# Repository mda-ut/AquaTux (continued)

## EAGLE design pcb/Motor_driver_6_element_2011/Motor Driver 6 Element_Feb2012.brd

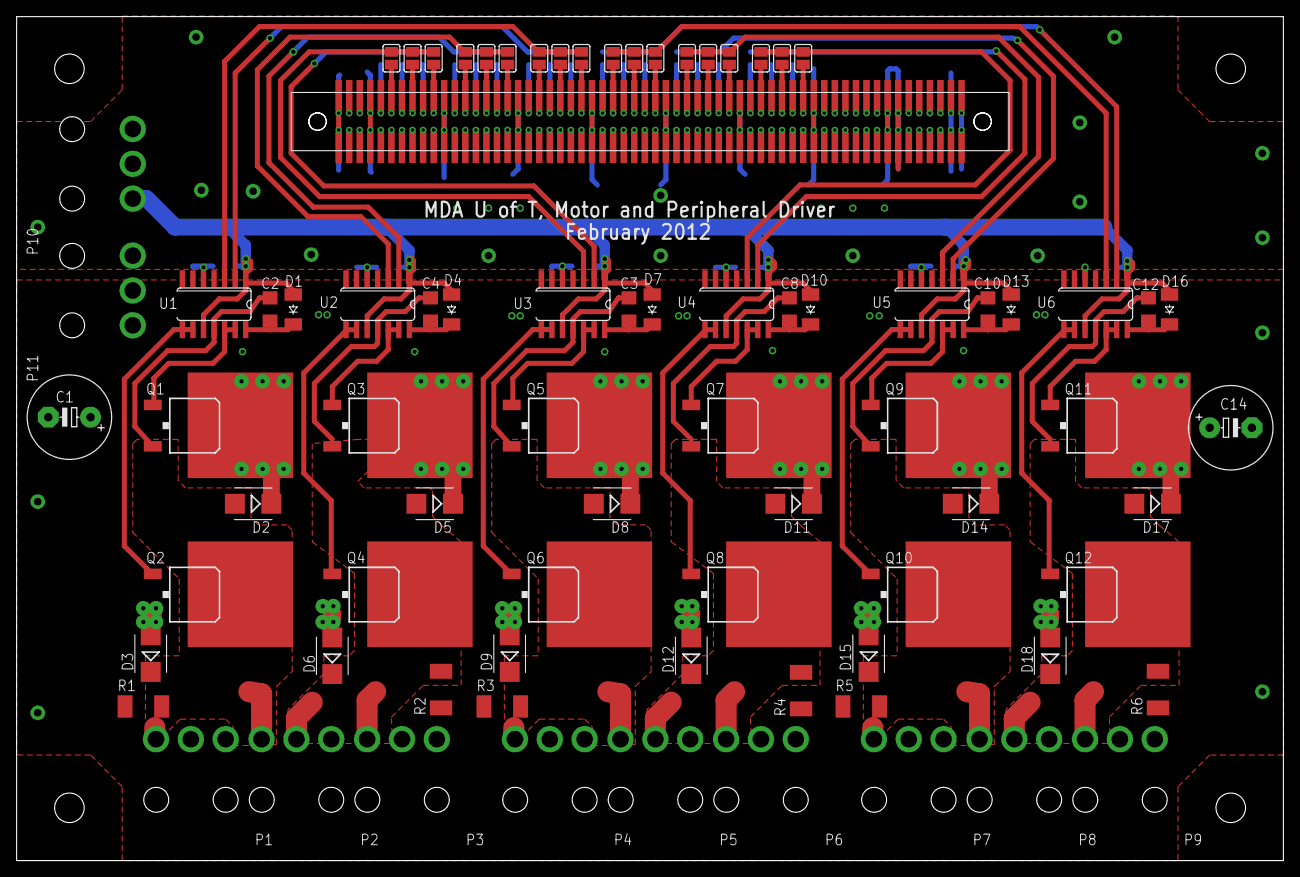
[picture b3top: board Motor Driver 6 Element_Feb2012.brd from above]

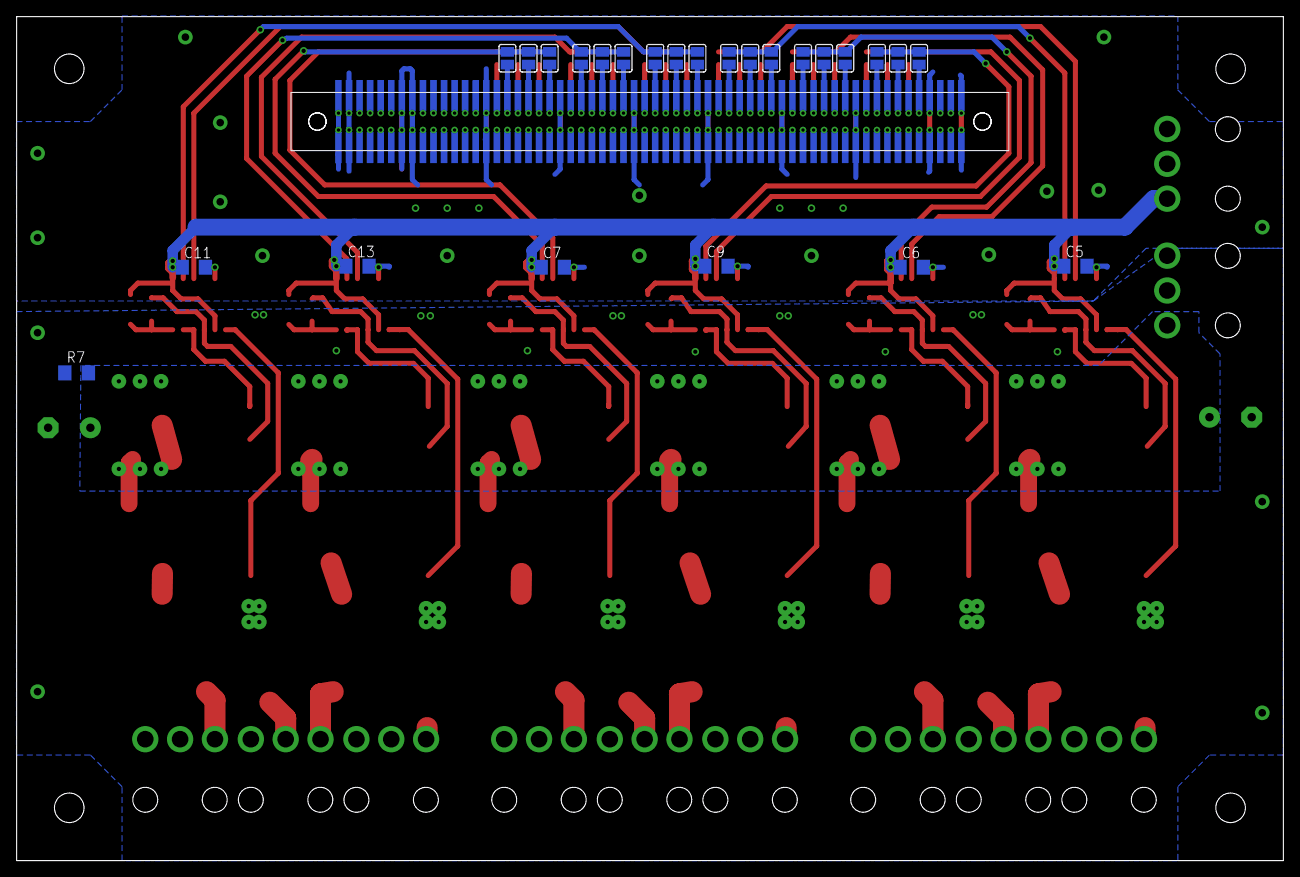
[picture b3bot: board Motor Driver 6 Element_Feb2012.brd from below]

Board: 2 copper layers, 152.4 x 101.5 mm, 106 parts (26 on the bottom side), 136 nets.

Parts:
C1, C14: >100uF; E5-10,5
C2, C3, C4, C8, C10, C12: 1uF; C1206
C5, C6, C7, C9, C11, C13: 10uF; C1206@1
D1, D4, D7, D10, D13, D16: CGRM4001-G; SOD-123_MINI-SMA
D2, D3, D5, D6, D8, D9, D11, D12, D14, D15, D17, D18: SMB
E$1, E$2: STACK-CONN-WIDEPITCH
P1, P2, P3, P4, P5, P6, P7, P8, P9, P10, P11: MOLEX_MINIFIT_JR_3CKT; 3CKT_MINIFIT_JR
Q1, Q2, Q3, Q4, Q5, Q6, Q7, Q8, Q9, Q10, Q11, Q12: IPB70N04S3; D-PAK_TO252AA
R1, R2, R3, R4, R5, R6: 1.5k; R2010
R7: R1206
SJ1, SJ2, SJ3, SJ4, SJ5, SJ6, SJ7, SJ8, SJ9, SJ10, SJ11, SJ12, SJ13, SJ14, SJ15, SJ16, SJ17, SJ18, SJ19, SJ21, SJ22, SJ23, SJ24, SJ25, SJ26, SJ27, SJ28, SJ29, SJ30, SJ31, SJ32, SJ33, SJ34, SJ35, SJ36, SJ37: SJ
U1, U2, U3, U4, U5, U6: LT1160CS; SOIC14

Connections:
+12V: C5.1, C6.1, C7.1, C9.1, C11.1, C13.1, D1.A, D4.A, D7.A, D10.A, D13.A, D16.A, P10.3, U1.1, U1.10, U2.1, U2.10, U3.1, U3.10, U4.1, U4.10, U5.1, U5.10, U6.1, U6.10
+24V: C1.+, C14.+, P11.3, R7.2
AGND: C1.-, C14.-, D3.A, D6.A, D9.A, D12.A, D15.A, D18.A, P1.3, P3.3, P4.3, P6.3, P7.3, P9.3, P11.2, Q2.3, Q4.3, Q6.3, Q8.3, Q10.3, Q12.3, R1.1, R2.1, R3.1, R4.1, R5.1, R6.1, R7.1, U1.6, U2.6, U3.6, U4.6, U5.6, U6.6
GND: C5.2, C6.2, C7.2, C9.2, C11.2, C13.2, E$1.A1, E$1.A2, E$1.A7, E$1.A8, E$1.A15, E$1.A22, E$1.A29, E$1.A36, E$1.A43, E$1.A50, E$1.A57, E$1.A60, E$1.B1, E$1.B2, E$1.B7, E$1.B8, E$1.B15, E$1.B22, E$1.B29, E$1.B36, E$1.B43, E$1.B50, E$1.B57, E$1.B60, E$2.A1, E$2.A4, E$2.A11, E$2.A18, E$2.A25, E$2.A32, E$2.A39, E$2.A46, E$2.A53, E$2.A54, E$2.A60, E$2.B1, E$2.B4, E$2.B11, E$2.B18, E$2.B25, E$2.B32, E$2.B39, E$2.B46, E$2.B53, E$2.B54, E$2.B59, E$2.B60, U1.5, U2.5, U3.5, U4.5, U5.5, U6.5
unnamed: C2.1, D1.C, U1.14
unnamed: SJ5.2, SJ6.2, SJ7.2, U3.3
unnamed: C3.1, D7.C, U3.14
unnamed: SJ2.2, SJ3.2, SJ4.2, U3.2
unnamed: SJ17.2, SJ18.2, U1.3
unnamed: Q1.1, U1.12, U1.13
unnamed: Q5.1, U3.12, U3.13
unnamed: C8.1, D10.C, U4.14
unnamed: Q8.1, U4.8, U4.9
unnamed: SJ21.2, U4.2
unnamed: SJ22.2, SJ23.2, SJ24.2, U4.3
unnamed: Q7.1, U4.12, U4.13
unnamed: C10.1, D13.C, U5.14
unnamed: SJ25.2, SJ26.2, SJ27.2, U5.3
unnamed: Q9.1, U5.12, U5.13
unnamed: C12.1, D16.C, U6.14
unnamed: Q12.1, U6.8, U6.9
unnamed: SJ31.2, SJ32.2, U6.3
unnamed: Q11.1, U6.12, U6.13
unnamed: C4.1, D4.C, U2.14
unnamed: Q4.1, U2.8, U2.9
unnamed: SJ9.2, SJ10.2, U2.2
unnamed: SJ12.2, SJ13.2, SJ14.2, U2.3
unnamed: Q3.1, U2.12, U2.13
unnamed: SJ1.2, SJ8.2, SJ15.2, U1.2
OUTA: C2.2, D2.A, D3.C, P1.1, P2.1, Q1.3, Q2.4, R1.2, U1.11
OUTA1: C3.2, D8.A, D9.C, P4.1, P5.1, Q5.3, Q6.4, R3.2, U3.11
OUTA2: C10.2, D14.A, D15.C, P7.1, P8.1, Q9.3, Q10.4, R5.2, U5.11
OUTB: C4.2, D5.A, D6.C, P2.2, P3.1, Q3.3, Q4.4, R2.2, U2.11
OUTB1: C8.2, D11.A, D12.C, P5.2, P6.1, Q7.3, Q8.4, R4.2, U4.11
OUTB2: C12.2, D17.A, D18.C, P8.2, P9.1, Q11.3, Q12.4, R6.2, U6.11
S$5: E$1.B55, E$2.B6, SJ7.1
S$6: Q2.1, U1.8, U1.9
S$11: Q6.1, U3.8, U3.9
S$12: E$1.B53, E$2.B8, SJ6.1
S$17: Q10.1, U5.8, U5.9
S$18: E$1.B51, E$2.B10, SJ5.1
S$19: E$1.B48, E$2.B13, SJ14.1
S$20: E$1.B46, E$2.B15, SJ13.1
S$21: E$1.B44, E$2.B17, SJ12.1
S$22: E$1.B41, E$2.B20, SJ18.1
S$23: E$1.B39, E$2.B22, SJ17.1
S$24: E$1.B37, E$2.B24
S$25: E$1.B34, E$2.B27, SJ33.1
S$26: E$1.B32, E$2.B29, SJ32.1
S$27: E$1.B30, E$2.B31, SJ31.1
S$28: E$1.B27, E$2.B34, SJ27.1
S$29: E$1.B25, E$2.B36, SJ26.1
S$30: E$1.B23, E$2.B38, SJ25.1
S$31: E$1.B20, E$2.B41, SJ24.1
S$32: E$1.B18, E$2.B43, SJ23.1
S$33: E$1.B16, E$2.B45, SJ22.1
S$34: E$1.B21, E$2.B40, SJ21.1
S$35: E$1.B19, E$2.B42, SJ19.1
S$36: E$1.B17, E$2.B44, SJ37.1
S$37: E$1.B24, E$2.B37, SJ30.1
S$38: E$1.B26, E$2.B35, SJ29.1
S$39: E$1.B28, E$2.B33, SJ28.1
S$40: E$1.B31, E$2.B30, SJ36.1
S$41: E$1.B33, E$2.B28, SJ35.1
S$42: E$1.B35, E$2.B26, SJ34.1
S$43: E$1.B38, E$2.B23, SJ15.1
S$44: E$1.B40, E$2.B21, SJ8.1
S$45: E$1.B42, E$2.B19, SJ1.1
S$46: E$1.B49, E$2.B12, SJ9.1
S$47: E$1.B47, E$2.B14, SJ10.1
S$48: E$1.B45, E$2.B16, SJ11.1
S$49: E$1.B52, E$2.B9, SJ4.1
S$50: E$1.B54, E$2.B7, SJ3.1
S$51: E$1.B56, E$2.B5, SJ2.1
S$53: SJ34.2, SJ35.2, SJ36.2, U6.2
S$54: SJ28.2, SJ29.2, SJ30.2, U5.2
S$57: E$1.A59, E$2.A2
S$58: E$1.A58, E$2.A3
S$60: E$1.A55, E$2.A6
S$61: E$1.A56, E$2.A5
S$62: E$1.A54, E$2.A7
S$63: E$1.A53, E$2.A8
S$64: E$1.A52, E$2.A9
S$65: E$1.A51, E$2.A10
S$67: E$1.A49, E$2.A12
S$68: E$1.A48, E$2.A13
S$69: E$1.A47, E$2.A14
S$70: E$1.A46, E$2.A15
S$71: E$1.A45, E$2.A16
S$72: E$1.A44, E$2.A17
S$74: E$1.A42, E$2.A19
S$75: E$1.A41, E$2.A20
S$76: E$1.A40, E$2.A21
S$77: E$1.A38, E$2.A23
S$78: E$1.A39, E$2.A22
S$79: E$1.A37, E$2.A24
S$81: E$1.A34, E$2.A27
S$82: E$1.A35, E$2.A26
S$83: E$1.A33, E$2.A28
S$84: E$1.A32, E$2.A29
S$85: E$1.A31, E$2.A30
S$86: E$1.A30, E$2.A31
S$88: E$1.A28, E$2.A33
S$89: E$1.A27, E$2.A34
S$90: E$1.A25, E$2.A36
S$91: E$1.A26, E$2.A35
S$92: E$1.A23, E$2.A38
S$93: E$1.A24, E$2.A37
S$95: E$1.A20, E$2.A41
S$96: E$1.A21, E$2.A40
S$97: E$1.A19, E$2.A42
S$98: E$1.A18, E$2.A43
S$99: E$1.A16, E$2.A45
S$100: E$1.A17, E$2.A44
S$102: E$1.A14, E$2.A47
S$103: E$1.A13, E$2.A48
S$104: E$1.A11, E$2.A50
S$105: E$1.A12, E$2.A49
S$106: E$1.A10, E$2.A51
S$107: E$1.A9, E$2.A52
S$109: E$1.A6, E$2.A55
S$111: E$1.A4, E$2.A57
S$112: E$1.A5, E$2.A56
S$113: E$1.A3, E$2.A58
S$117: E$1.B59, E$2.B2
S$119: E$1.B58, E$2.B3
S$126: E$1.B13, E$2.B48
S$127: E$1.B14, E$2.B47
S$128: E$1.B11, E$2.B50
S$129: E$1.B12, E$2.B49
S$130: E$1.B10, E$2.B51
S$132: E$1.B9, E$2.B52
S$133: E$1.B6, E$2.B55
S$135: E$1.B5, E$2.B56
S$136: E$1.B4, E$2.B57
S$137: E$1.B3, E$2.B58

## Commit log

2014-05-15 Removed HistogramFilter, AdvancedFilter, Hue_Box
2014-05-15 Removed a few more extraneous things.
2014-05-15 Removed terrible flags in mvWatershedFilter. Replaced with nicer named flags.
2014-05-19 Removes mvShaps.h and mvShapes.cpp
2014-05-19 Removes extra settings file
2014-05-27 Adds new file for vision documentation
2014-06-05 added gitignore
2014-06-29 Update mvWaterShed.cpp
    Should fix rare failure on assert(N >= k) in kmeans
2014-06-29 Removed u_gate, added goalpost to sim, ignore *~ files
2014-06-29 renamed frame task files to goalpost task files
2014-06-29 more renaming of frame task to goalpost task
2014-06-29 ahhhhhh namesss
2014-06-29 added goalpost vision module
2014-07-02 fixed typo in vision_goalpost so code compiles
2014-07-05 Changes on Rose's laptop for debug
2014-07-06 Testing committing from my computer - added a folder for SONAR Verilog code.
2014-07-06 Embedded 2013 2014 Code and Documentation
2014-07-06 Reverts back to static libraries, fixed the milions of pencv lib warning messages
2014-07-06 (INCOMPLETE) adds common.h for common debug defines
2014-07-06 (INCOMPLETE) changes to compile aquatux properly
2014-07-06 Revert "Reverts back to static libraries, fixed the milions of pencv lib warning messages"
    This reverts commit 8a705e9f2670226f54c2e2088fc1b48ccdcde0d2.
    Conflicts:
    software/interface/Makefile
2014-07-06 Revert back to shared libraries, fix compile warnings
2014-07-06 Removed some aquatux setting files
2014-07-06 added debug levels, changed setting files, fixed debugging for contour and path module
2014-07-08 Changes to get Ritchie closer to compiling
2014-07-10 Changes match_circle to new debug and params infrastructure
2014-07-10 Removes annoying space
2014-07-10 Removes more annoying spaces
2014-07-18 Fixed the Sin Function generator.
2014-07-29 fixed compilation issue that fixed ritchie's compile but broke everyone else's, and added missing settings reqd for match_rectangle to several task settings
2014-07-29 random changes for competition hacks
2014-07-30 added temp print statements
2014-07-30 hacky as fuck
2014-07-30 Started to document pieces of the vision code
2014-07-30 hacky hack
2014-07-30 added path (gate) task depth check
2014-07-31 path might be working?
2014-07-31 cleaned up path task and added file timestamp
2014-07-31 removed unnecessary "full detect" for gate task in path task file
    Please enter the commit message for your changes. Lines starting
2014-07-31 removes random text in task path why the fuck are they there
2014-07-31 Netbook changes
2014-07-31 changed path task depth and speed
2014-07-31 set up debugging for goalpost vision
2014-07-31 Modified the task a bit
2014-07-31 Changed the MDASin to 30kHz from 22kHz
2014-07-31 butchering goalpost code
2014-07-31 path task ready for dolphin test
2014-08-01 goalpost now works in sim
2014-08-01 more path hacks
2014-08-01 testing path with amber lens
2014-08-01 set up buoy vision debug
2014-08-01 set up circle detection for buoy vision
2014-08-01 simplified path
2014-08-01 using pos_angle to align path
2014-08-01 Update task_path.cpp
    Compile fix
2014-08-01 semi final run this is going to be bad
2014-08-01 gate then surface
2014-08-01 ram the gate then ram the goalpost ohgod
2014-08-01 change depth to 250
2014-08-02 added timer and surface after path
2014-08-02 Now surfaces after goalpost
